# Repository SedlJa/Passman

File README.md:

# Passman

Passman is an embedded password manager with a custom hardware device and a desktop companion application. The project is developed as part of a master's thesis at CTU FEE and combines an ESP32-S3 based device, biometric authentication, local password storage, USB serial communication, and a Python desktop GUI.

The goal is to create a portable hardware password manager that stores credentials locally on the device and allows the user to view, edit, upload, and download the password database through a dedicated desktop application.

## Repository Structure

```text
HW/                 Hardware design files
  pcb/              KiCad PCB project, schematics, BOM and assembly outputs
  Fusion/           3D enclosure models and exported STL files
  block_diagram.svg System block diagram
  PassMan_schematic_v2.1.pdf
  pcb_v2.png
  pcb_2v1.png

SW/
  firmware/         ESP32-S3 firmware built with PlatformIO
  app/              Python / PySide6 desktop application

_docs/              Project documentation and supporting materials
```

## Hardware

The hardware part contains the custom PCB and enclosure design for the Passman device.

Main components:

- ESP32-S3-WROOM-1 module
- 128x64 OLED display with SH1106 controller
- Fingerprint sensor connected over UART
- Rotary encoder with push button
- USB-C connector for power, flashing, and serial communication
- Li-Po battery input and charging circuit
- MCP73831 Li-Po charger
- STBB1-APUR voltage regulator
- User LEDs and reset / boot buttons

Hardware files include:

- KiCad schematic and PCB project
- PDF schematic export
- BOM
- Assembly output
- PCB preview images
- Fusion 360 enclosure exports
- STL files for 3D printing

## Firmware

Firmware is located in `SW/firmware` and is built with PlatformIO.

Target board:

```ini
esp32-s3-devkitm-1
```

Framework:

```ini
Arduino
```

Main firmware features:

- Fingerprint based unlock
- PIN fallback after failed fingerprint attempts
- OLED menu system
- Rotary encoder navigation
- Local password database stored in SPIFFS
- USB serial communication with the desktop app
- Device information reporting
- Password database load, upload, save, and delete actions

Used libraries:

- Ai Esp32 Rotary Encoder
- Adafruit SH110X
- Adafruit GFX
- Adafruit Fingerprint Sensor Library
- ArduinoJson

### Build and Upload Firmware

```bash
cd SW/firmware
pio run
pio run -t upload
pio run -t uploadfs
```

Serial monitor:

```bash
pio device monitor -b 115200
```

## Desktop Application

The desktop app is located in `SW/app`. It is written in Python using PySide6 and communicates with the Passman device over a serial port.

Main app features:

- COM port search and connection handling
- Device information display
- Load password database from device
- Add, edit, and delete password entries
- Upload database back to device
- Password visibility toggle
- Password generator
- Local clearing of displayed data after disconnect

### Run the App

```bash
cd SW/app
python3 -m venv env
source env/bin/activate
pip install -r requirements.txt
python app.py
```

Python dependencies are listed in `SW/app/requirements.txt`.

## Communication

The desktop application and firmware communicate over USB serial at `115200 baud`.

Supported commands include:

- `info` - read device information
- `load` - load database from the device
- `download` - send updated database to the device
- `disconnect` - close the app-device session

## Security Notice

This project is currently a prototype / thesis implementation. Before using it for real credentials, the security model should be reviewed and hardened.

## Author

- Author: Bc. Jan Sedlak
- Supervisor: Ing. Ondrej Nentvich, Ph.D.
- University: Czech Technical University in Prague
- Faculty: Faculty of Electrical Engineering
- Field: Internet of Things Technology
- Department: Department of Radioelectronics

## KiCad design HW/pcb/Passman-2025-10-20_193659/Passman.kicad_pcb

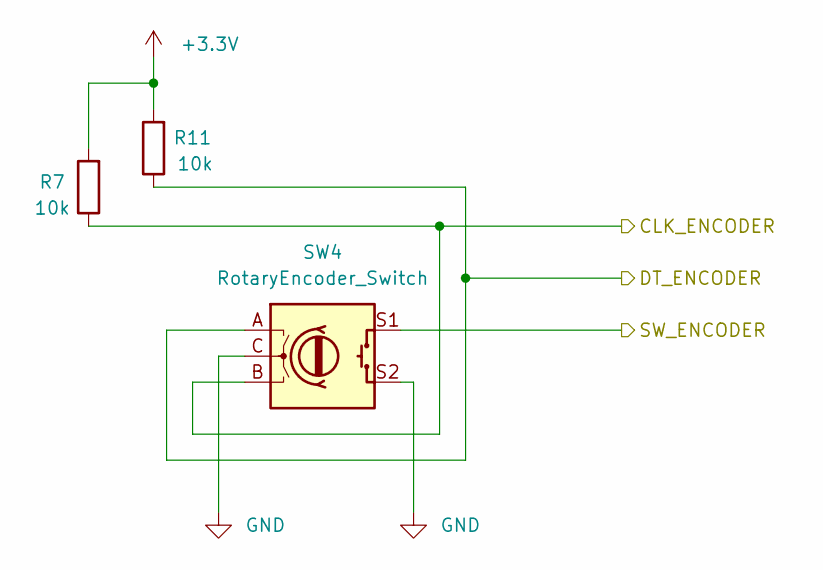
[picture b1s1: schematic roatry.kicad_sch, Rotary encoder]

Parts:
R7, R11: 10k; R_0805_2012Metric
SW4: RotaryEncoder_Switch; RotaryEncoder_Bourns_Horizontal_PEC09-2xxxF-Sxxxx

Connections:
+3.3V: R7.2, R11.2; also elsewhere on the board
/ESP32_S3/CLK_ENCODER: R7.1, SW4.B; also elsewhere on the board
/ESP32_S3/DT_ENCODER: R11.1, SW4.A; also elsewhere on the board
/ESP32_S3/SW_ENCODER: SW4.S1; also elsewhere on the board

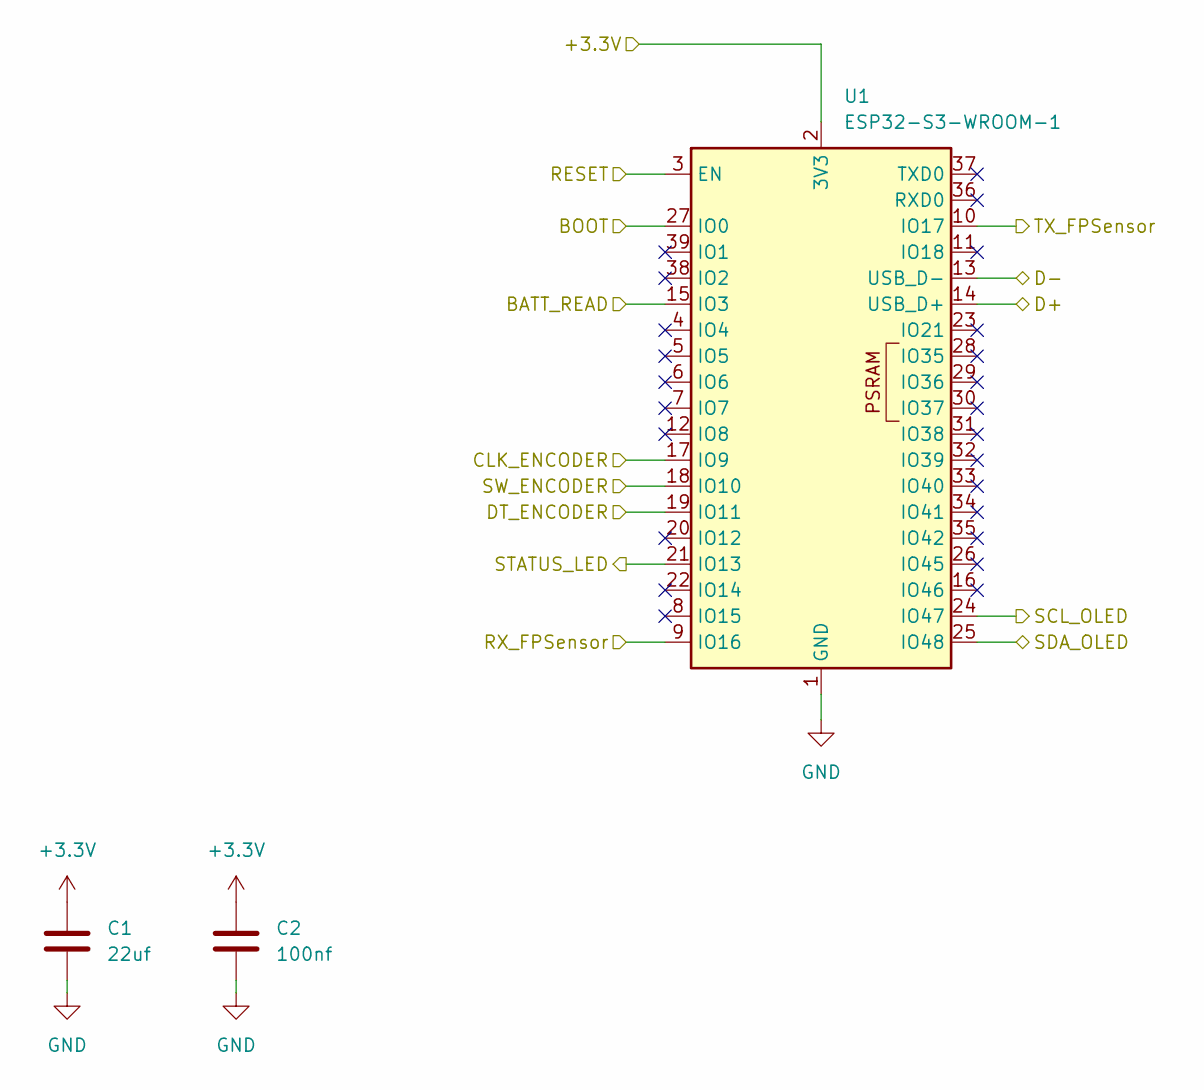
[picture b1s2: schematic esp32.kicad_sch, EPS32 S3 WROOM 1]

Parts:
C1: 22uf; C_0805_2012Metric_Pad1.18x1.45mm_HandSolder
C2: 100nf; C_0805_2012Metric_Pad1.18x1.45mm_HandSolder
U1: ESP32-S3-WROOM-1

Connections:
+3.3V: C1.1, C2.1, U1.2 (3V3); also elsewhere on the board
/ESP32_S3/BATT_READ: U1.15 (IO3); also elsewhere on the board
/ESP32_S3/BOOT: U1.27 (IO0); also elsewhere on the board
/ESP32_S3/CLK_ENCODER: U1.17 (IO9); also elsewhere on the board
/ESP32_S3/D+: U1.14 (USB_D+); also elsewhere on the board
/ESP32_S3/D-: U1.13 (USB_D-); also elsewhere on the board
/ESP32_S3/DT_ENCODER: U1.19 (IO11); also elsewhere on the board
/ESP32_S3/RESET: U1.3 (EN); also elsewhere on the board
/ESP32_S3/RX_FPSensor: U1.9 (IO16); also elsewhere on the board
/ESP32_S3/SCL_OLED: U1.24 (IO47); also elsewhere on the board
/ESP32_S3/SDA_OLED: U1.25 (IO48); also elsewhere on the board
/ESP32_S3/SW_ENCODER: U1.18 (IO10); also elsewhere on the board
/ESP32_S3/TX_FPSensor: U1.10 (IO17); also elsewhere on the board
/ESP32_S3/USER_LED: U1.21 (IO13); also elsewhere on the board

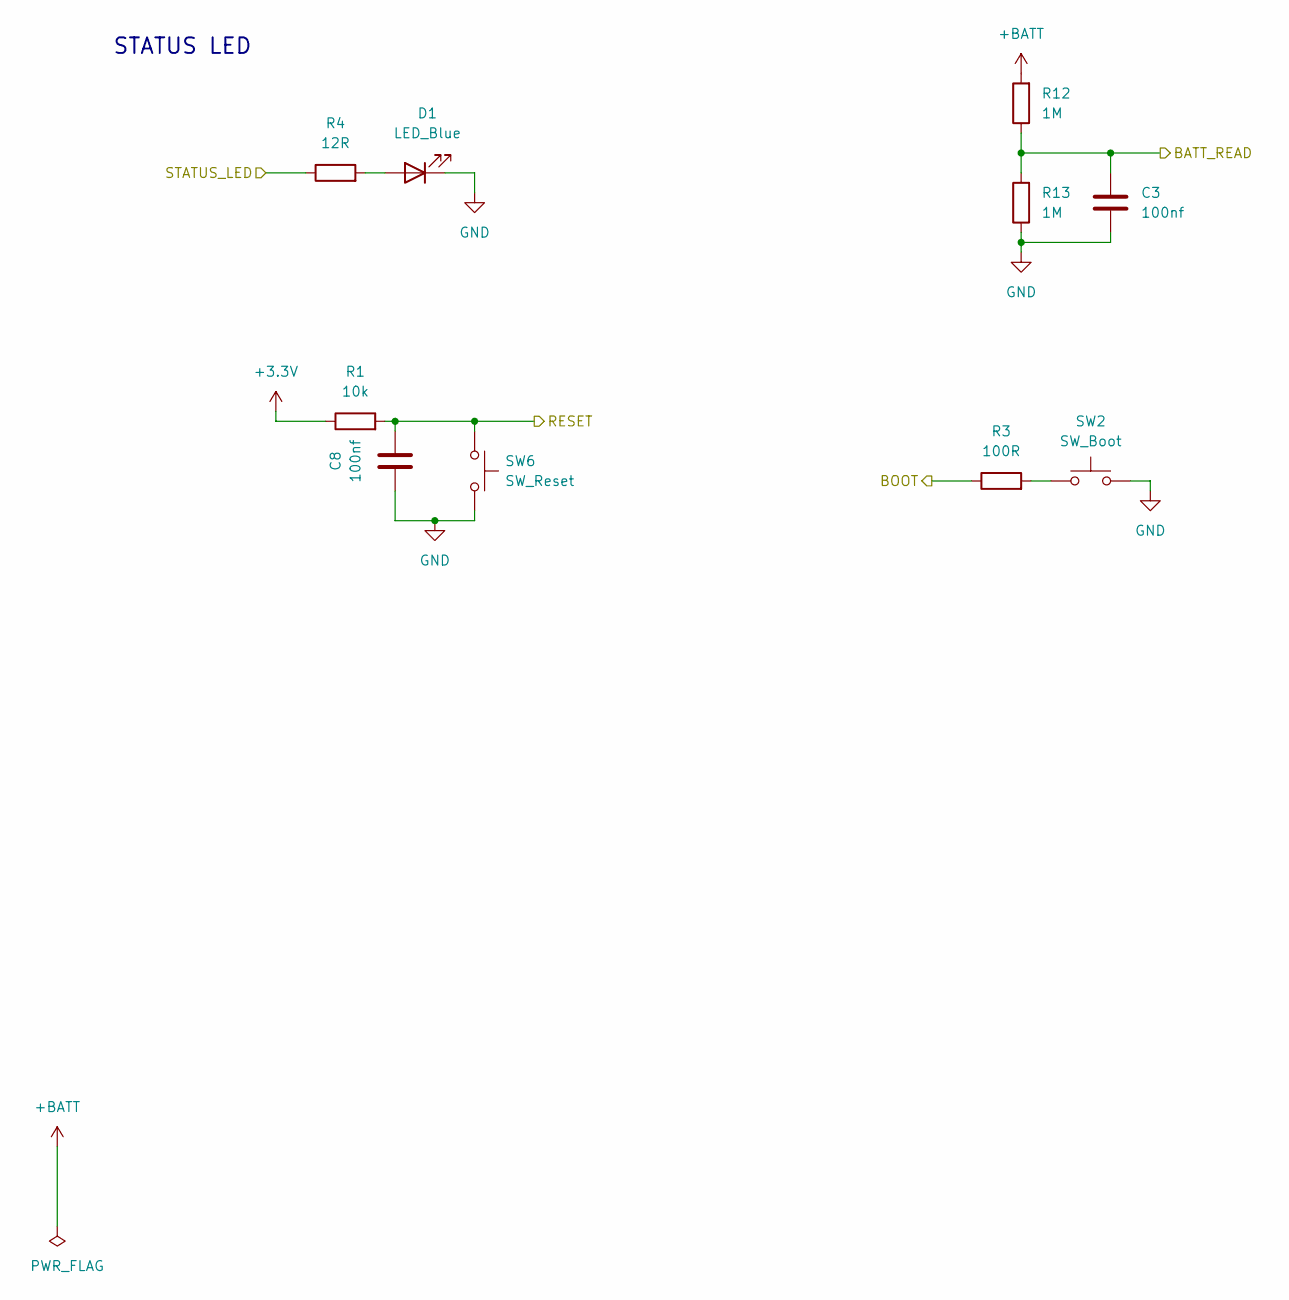
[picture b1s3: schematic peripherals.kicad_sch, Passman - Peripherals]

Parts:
C3, C8: 100nf; C_0805_2012Metric_Pad1.18x1.45mm_HandSolder
D1: LED_Blue; LED_0805_2012Metric_Pad1.15x1.40mm_HandSolder
R1: 10k; R_0805_2012Metric
R3: 100R; R_0805_2012Metric
R4: 12R; R_0805_2012Metric
R12, R13: 1M; R_0805_2012Metric
SW2: SW_Boot; SW_PUSH_6mm_H5mm
SW6: SW_Reset; SW_PUSH_6mm_H5mm

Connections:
+3.3V: R1.1; also elsewhere on the board
+BATT: R12.2; also elsewhere on the board
/ESP32_S3/BATT_READ: C3.1, R12.1, R13.2; also elsewhere on the board
/ESP32_S3/BOOT: R3.1; also elsewhere on the board
/ESP32_S3/RESET: C8.2, R1.2, SW6.1; also elsewhere on the board
/ESP32_S3/USER_LED: R4.1; also elsewhere on the board
unnamed: D1.2 (A), R4.2
unnamed: R3.2, SW2.1

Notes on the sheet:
STATUS LED

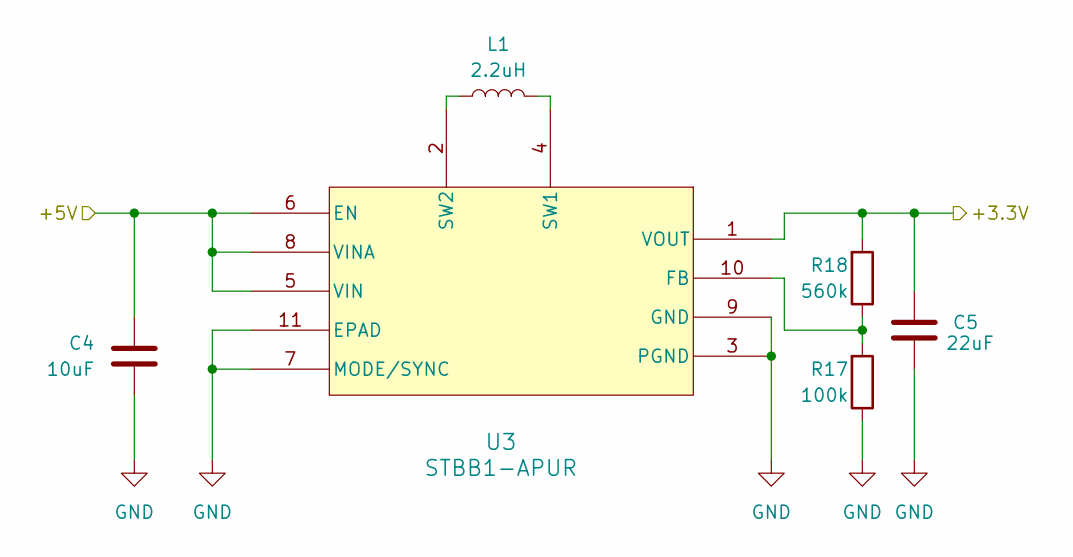
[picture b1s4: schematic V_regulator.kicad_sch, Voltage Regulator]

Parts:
C4: 10uF; C_0805_2012Metric_Pad1.18x1.45mm_HandSolder
C5: 22uF; C_0805_2012Metric_Pad1.18x1.45mm_HandSolder
L1: 2.2uH; L_Coilcraft_XxL4020
R17: 100k; R_0805_2012Metric
R18: 560k; R_0805_2012Metric
U3: STBB1-APUR; SON_B1-APUR_STM

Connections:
+3.3V: C5.1, R18.2, U3.1 (VOUT); also elsewhere on the board
+5V: C4.1, U3.5 (VIN), U3.6 (EN), U3.8 (VINA); also elsewhere on the board
unnamed: R17.2, R18.1, U3.10 (FB)
unnamed: L1.1, U3.4 (SW1)
unnamed: L1.2, U3.2 (SW2)

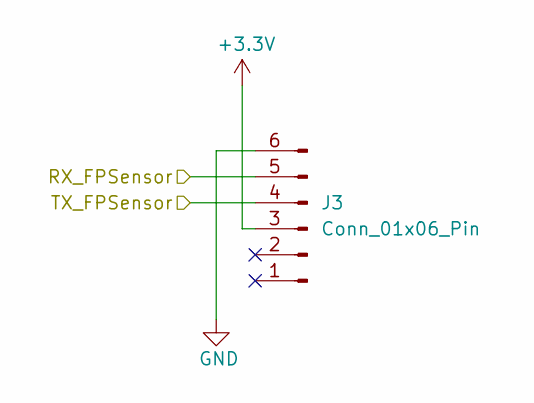
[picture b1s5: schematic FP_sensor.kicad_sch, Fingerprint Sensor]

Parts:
J3: Conn_01x06_Pin; JST_SH_BM06B-SRSS-TB_1x06-1MP_P1.00mm_Vertical

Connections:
+3.3V: J3.3; also elsewhere on the board
/ESP32_S3/RX_FPSensor: J3.5; also elsewhere on the board
/ESP32_S3/TX_FPSensor: J3.4; also elsewhere on the board

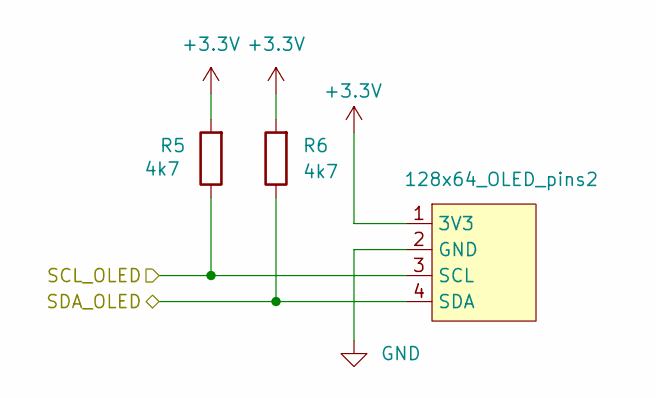
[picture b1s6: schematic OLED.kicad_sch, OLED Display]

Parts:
128x64_OLED_pins2: PinHeader_1x04_P2.54mm_Vertical
R5, R6: 4k7; R_0805_2012Metric

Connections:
+3.3V: 128x64_OLED_pins2.1 (3V3), R5.2, R6.2; also elsewhere on the board
/ESP32_S3/SCL_OLED: 128x64_OLED_pins2.3 (SCL), R5.1; also elsewhere on the board
/ESP32_S3/SDA_OLED: 128x64_OLED_pins2.4 (SDA), R6.1; also elsewhere on the board

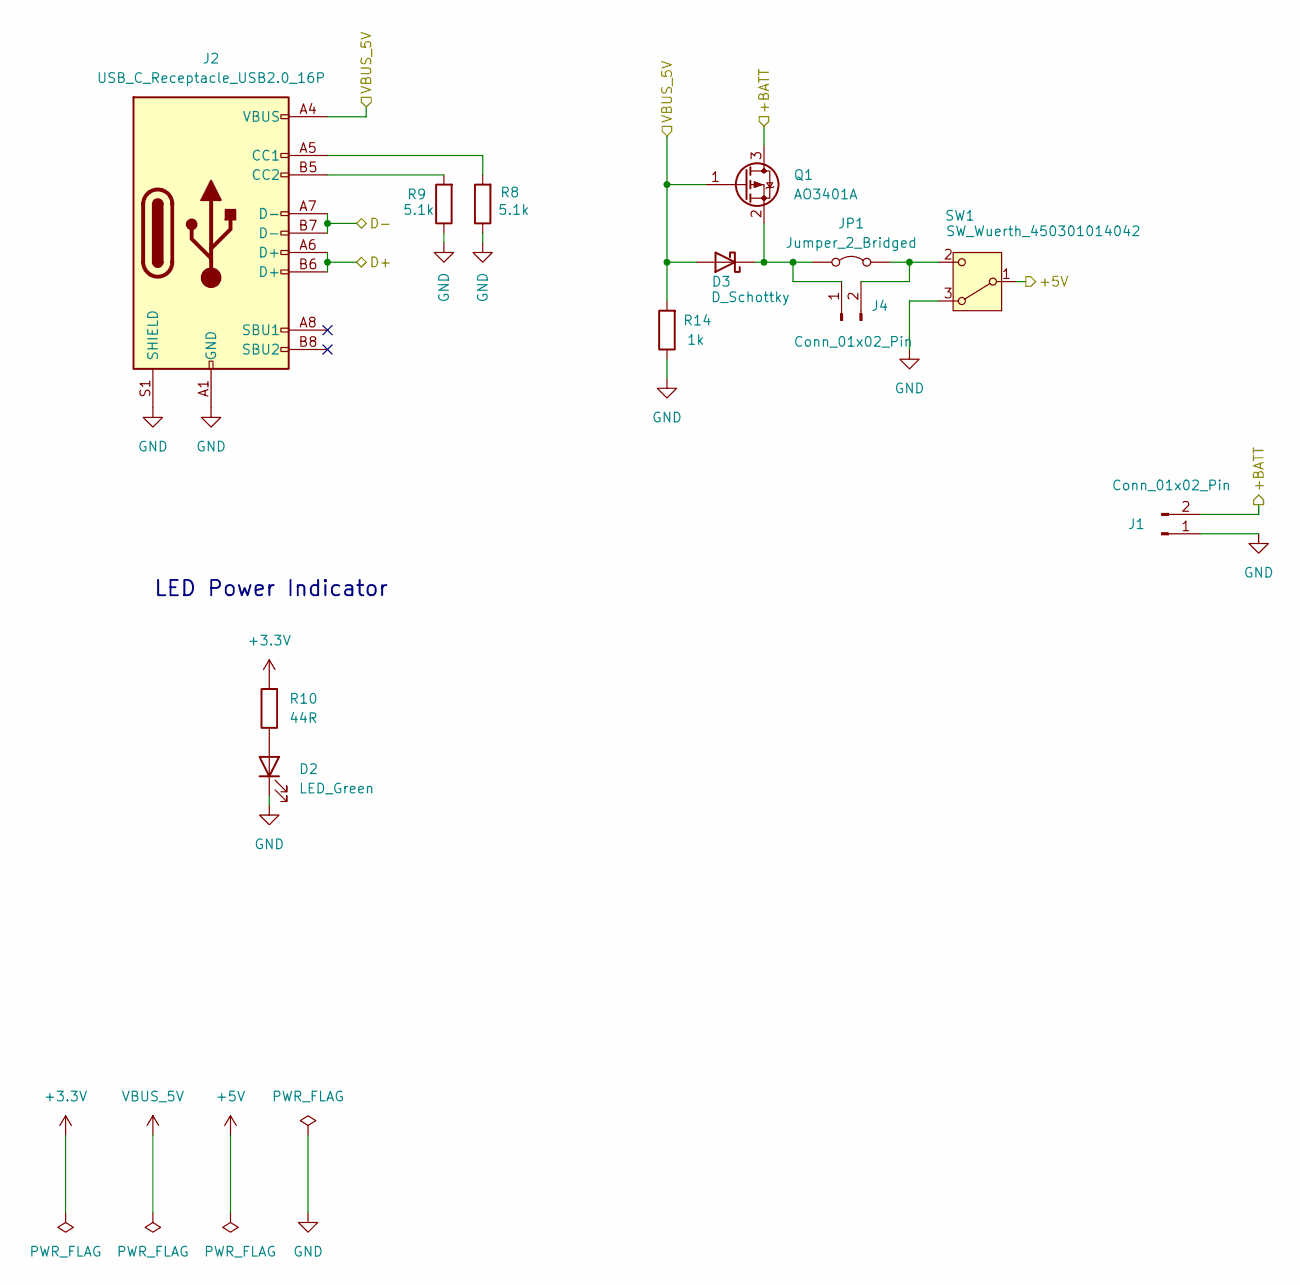
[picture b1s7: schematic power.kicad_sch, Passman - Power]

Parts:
D2: LED_Green; LED_0805_2012Metric_Pad1.15x1.40mm_HandSolder
D3: D_Schottky; D_0805_2012Metric_Pad1.15x1.40mm_HandSolder
J1: Conn_01x02_Pin; JST_SH_BM02B-SRSS-TB_1x02-1MP_P1.00mm_Vertical
J2: USB_C_Receptacle_USB2.0_16P; USB_C_Receptacle_GCT_USB4105-xx-A_16P_TopMnt_Horizontal
J4: Conn_01x02_Pin; PinHeader_1x02_P1.27mm_Vertical
JP1: Jumper_2_Bridged; SolderJumper-2_P1.3mm_Open_TrianglePad1.0x1.5mm
Q1: AO3401A; SOT-23
R8, R9: 5.1k; R_0805_2012Metric
R10: 44R; R_0805_2012Metric
R14: 1k; R_0805_2012Metric
SW1: SW_Wuerth_450301014042; SW_Slide-03_Wuerth-WS-SLTV_10x2.5x6.4_P2.54mm

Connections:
+3.3V: R10.2; also elsewhere on the board
+5V: SW1.1 (B); also elsewhere on the board
+BATT: J1.2, Q1.3 (D); also elsewhere on the board
/ESP32_S3/D+: J2.A6 (D+), J2.B6 (D+); also elsewhere on the board
/ESP32_S3/D-: J2.A7 (D-), J2.B7 (D-); also elsewhere on the board
unnamed: D2.2 (A), R10.1
unnamed: D3.1 (K), J4.1, JP1.1 (A), Q1.2 (S)
unnamed: J4.2, JP1.2 (B), SW1.2 (C)
VBUS_5V: D3.2 (A), J2.A4 (VBUS), J2.A9 (VBUS), J2.B4 (VBUS), J2.B9 (VBUS), Q1.1 (G), R14.2; also elsewhere on the board

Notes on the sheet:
LED Power Indicator

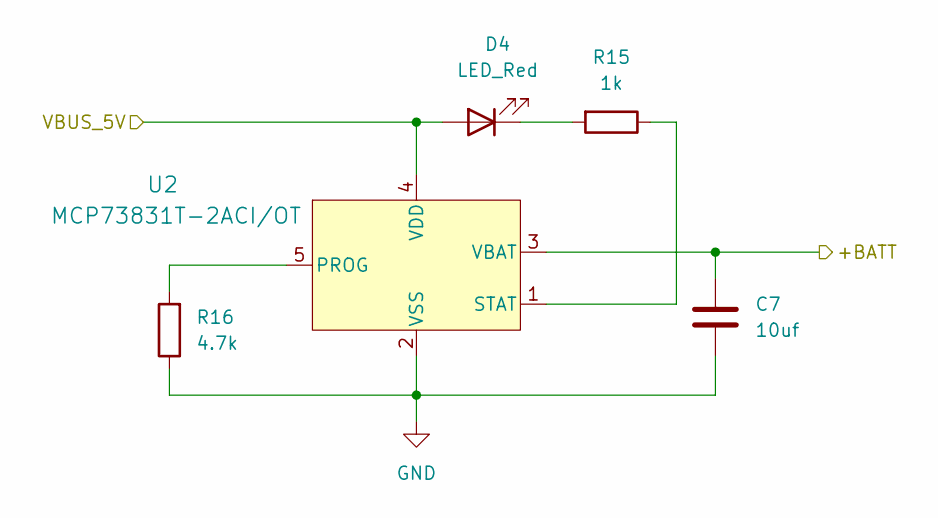
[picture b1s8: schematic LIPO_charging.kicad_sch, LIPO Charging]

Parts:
C7: 10uf; C_0805_2012Metric_Pad1.18x1.45mm_HandSolder
D4: LED_Red; LED_0805_2012Metric_Pad1.15x1.40mm_HandSolder
R15: 1k; R_0805_2012Metric
R16: 4.7k; R_0805_2012Metric
U2: MCP73831T-2ACI/OT; SOT95P280X145-5N

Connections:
+BATT: C7.1, U2.3 (VBAT); also elsewhere on the board
unnamed: D4.1 (K), R15.2
unnamed: R16.2, U2.5 (PROG)
unnamed: R15.1, U2.1 (STAT)
VBUS_5V: D4.2 (A), U2.4 (VDD); also elsewhere on the board

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
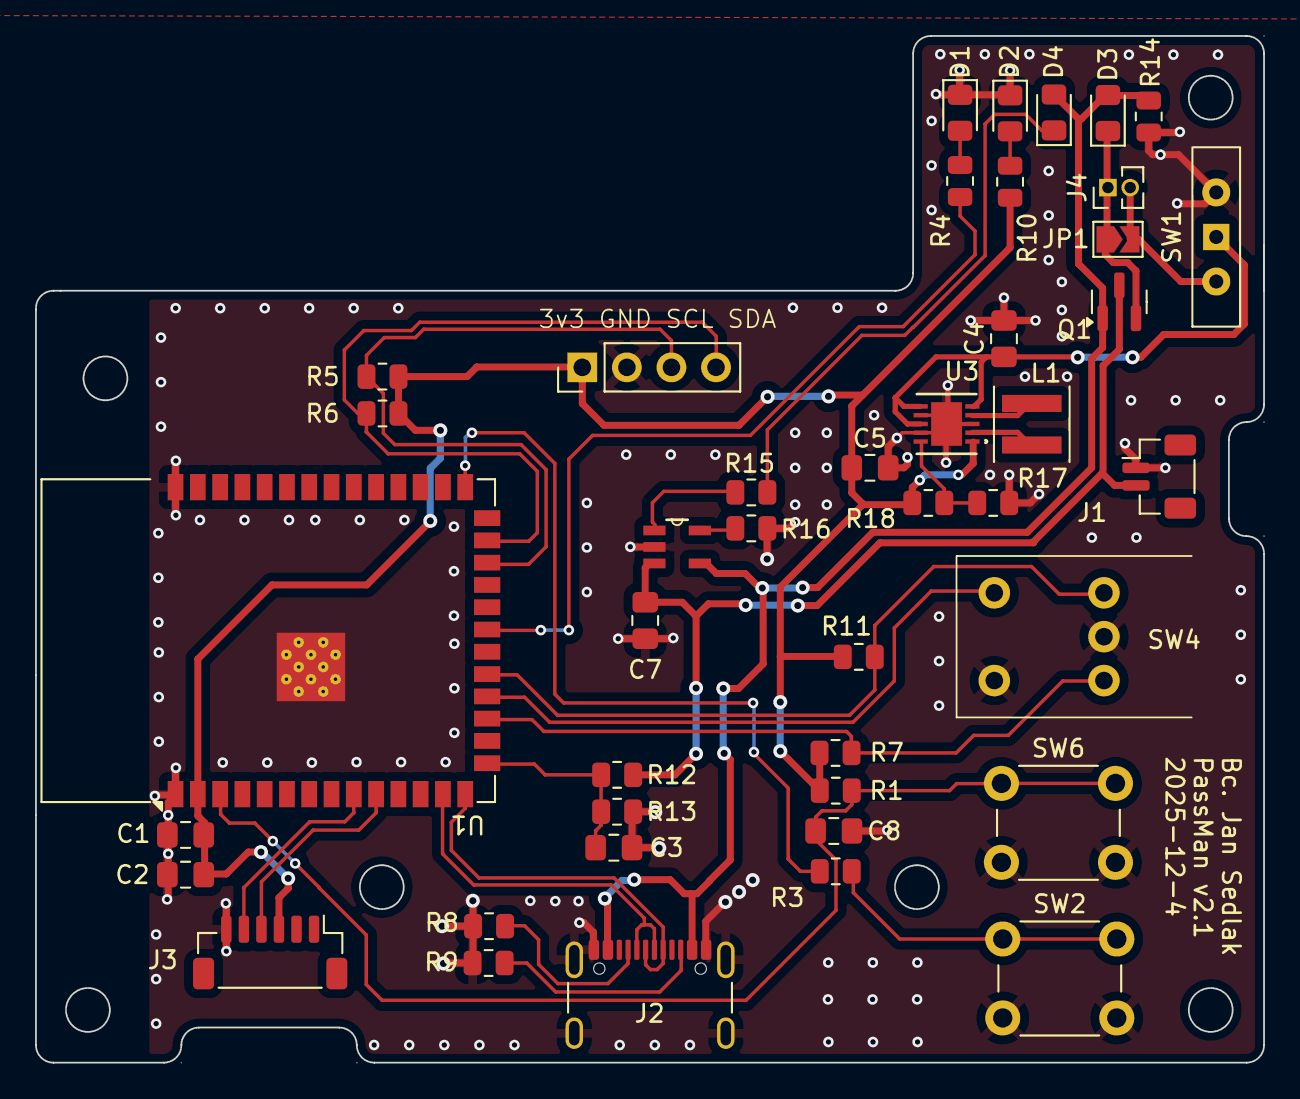
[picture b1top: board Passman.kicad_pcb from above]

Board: 2 copper layers, 70.0 x 58.5 mm, 43 parts (0 on the bottom side), 31 nets.

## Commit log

2024-11-29 Initialization comit
2024-11-29 _docs commit
2024-12-03 FW init
2025-03-26 added _docs folder
2025-04-03 added summary
2025-04-03 updated summary
2025-04-30 update summary
2025-04-30 added .gitignore
2025-06-01 added esp32 documentation
2025-06-15 added datasheets
2025-06-15 Firmware directory initialization, oled and rotary drivers added
2025-06-27 Pokus o navigaci v menu
2025-06-27 update author page
2025-06-30 initial commit, added authentication lib
2025-07-07 Update PIN menu
2025-07-19 Added images for main menu, main menu is now static UI
2025-07-19 Deleted unnecessary hex-files
2025-07-20 added connecting pages images, updated Connect option
2025-07-22 added oled i2c finder utility
2025-07-22 init fingerprint function - fpcheck, this function contains basic func to handle fp sensor operations
2025-07-27 added fingerprint sensor and featured utilities
2025-07-28 updated gitignore
2025-07-29 fpSerial turn off after unlock
2025-09-11 added connection/disconnection pages
2025-09-12 WebApp initial commit
2025-10-14 webapp deleted -> Qt app inc
2025-10-17 new repo structure
2025-10-17 deleted _images folder
2025-10-17 update 17/10/2025
    Updated project description and repository structure.
2025-10-17 update 17/10/2025
    Added section for the first prototype with an image.
2025-10-17 Update .gitignore to change Fusion path
2025-10-18 added pcb 3D model to HW
2025-10-18 updated pcb img
2025-10-18 update 18/10/2025
2025-10-18 Added database page & files
2025-10-18 added serial input, parse function
2025-10-22 updated schematic_v2
2025-10-22 desktop app init
2025-10-22 device-to-app communication, load database from device
2025-10-23 added Load db and Upload db buttons
2025-10-23 updated schematic
2025-10-24 Updated device-app comm
2025-10-24 added buttons, list of db entries
2025-10-25 added encryption files to app, upload/download menu for firmware
2025-10-25 fully functional communication device-app
2025-10-25 New app visual
2025-10-27 added password generator feature
2025-10-27 added requirements.txt
2025-10-27 added app icon
2025-10-29 added minor updates
2025-10-29 added encryption functions to app, fw
2025-11-06 functional Device -> App encrypted communication of one entry, decrypted in app and saved
2025-11-06 Uploading DB to app now for entire database
2025-11-07 added Delete ALL button - deletes entire database
2025-11-07 Functional encrypted communication both ways
2025-11-07 added psw visibilit toggle button, new list layout
2025-11-10 app updates - psw visibility, edit entry, ID not editable
2025-11-10 app code cleaning
2025-11-10 updated communication with app
2025-11-17 working state
2025-11-28 added pcb parts placement
2026-01-19 own pcb v2.1 alivegit status! encoder TBD
2026-01-19 comment
2026-01-19 Update main.cpp
    next try
2026-01-19 update rotary encoder
2026-02-12 new menu pics xd
2026-02-13 funkcni menu
2026-02-14 new menu, SPIFFS database
2026-02-14 added device.json
2026-02-17 adde new features to app-device exp
2026-02-21 recreated Application, added info command
2026-02-21 connection toggle button added
2026-02-22 new toggle button
2026-02-22 list edit
2026-02-25 added battery read function
2026-03-13 cleaning
2026-03-13 added pin function
2026-03-13 Added feature with pin unlock and block timer after 4 fails
2026-03-13 5 tries, battery lvl adjustment
2026-03-19 docs
2026-03-24 add fingerprint function added
2026-03-24 added match not found page
2026-03-26 new fw_diagram
2026-04-17 added docs
2026-05-17 updates pred odevzdanim
2026-05-19 Update encryption key handling
2026-05-19 Revert "Merge pull request #12 from SedlJa/feature/newmenu"
    This reverts commit 42eee86a80cdcba1802b2d28394379cd1a876b0e, reversing
    changes made to 6937fb5cfae5ef343e6ff9fafa659c53ed70236d.
2026-05-19 Revert "Merge feature/newmenu into main"
    This reverts commit 6937fb5cfae5ef343e6ff9fafa659c53ed70236d, reversing
    changes made to 4d8194ec5ef69cebd220a0963e4b2b26cc86caff.
2026-05-19 Replace main with feature/newmenu content
2026-05-19 final updates
2026-05-20 Clean up repository ignore rules
2026-05-20 upload pcb docs
